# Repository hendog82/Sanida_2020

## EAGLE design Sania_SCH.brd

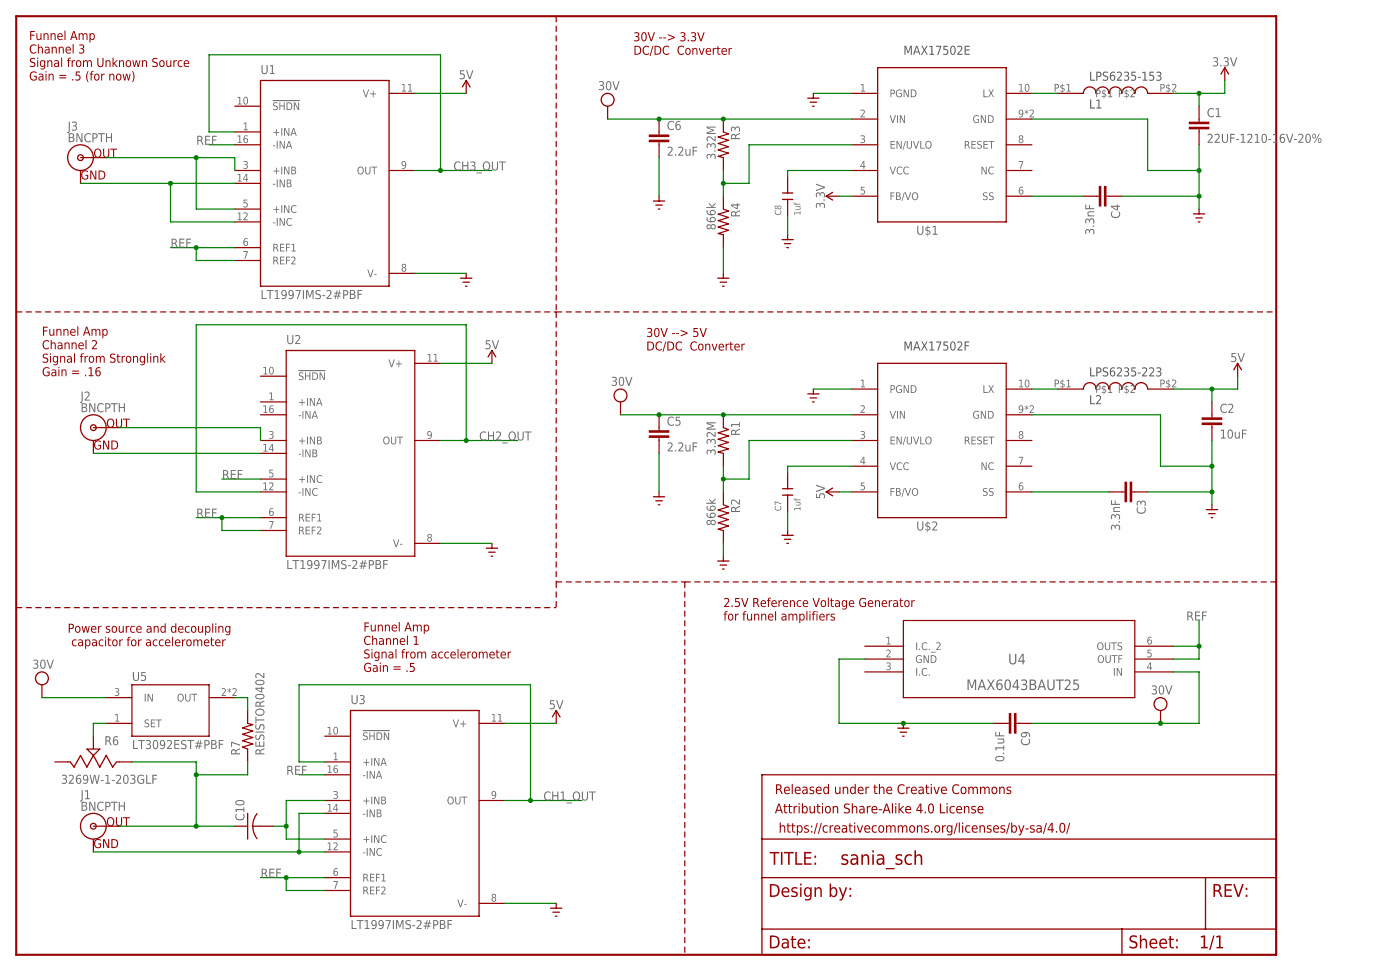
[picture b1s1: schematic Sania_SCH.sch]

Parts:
C1: 22UF-1210-16V-20%; 1210
C2: 10uF; 1210
C3, C4: 3.3nF; 0603
C5, C6: 2.2uF; 1206
C7, C8: 1uf; C0805
C9: 0.1uF; 0603
C10: C-USC0603; C0603
FRAME1: FRAME-LETTER; CREATIVE_COMMONS
J1, J2, J3: BNCPTH; BNC
L1: LPS6235-153; LPS6235
L2: LPS6235-223; LPS6235
R1, R3: 3.32M; R0805
R2, R4: 866k; R0805
R6: 3269W-1-203GLF
R7: RESISTOR0402; 0402-RES
U1, U2, U3: LT1997IMS-2#PBF; SOP50P490X110-12N
U4: MAX6043BAUT25; 21-0058I
U5: LT3092EST#PBF; IC_LT3092EST#PBF
U$1: MAX17502E; SON50P200X300X80-11T90X200N
U$2: MAX17502F; SON50P200X300X80-11T90X200N

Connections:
3.3V: C1.1, L1.P$2, U$1.5 (FB/VO)
5V: C2.1, L2.P$2, U1.11 (V+), U2.11 (V+), U3.11 (V+), U$2.5 (FB/VO)
CH1_OUT: U3.1 (+INA), U3.9 (OUT)
CH2_OUT: U2.9 (OUT), U2.12 (-INC)
CH3_OUT: U1.1 (+INA), U1.9 (OUT)
GND: C1.2, C2.2, C3.1, C4.1, C5.2, C6.2, C7.1, C8.1, C9.2, R2.2, R4.2, U1.8 (V-), U2.8 (V-), U3.8 (V-), U4.2 (GND), U$1.1 (PGND), U$1.9 (GND), U$1.11 (GND), U$2.1 (PGND), U$2.9 (GND), U$2.11 (GND)
unnamed: L1.P$1, U$1.10 (LX)
unnamed: L2.P$1, U$2.10 (LX)
unnamed: C8.2, U$1.4 (VCC)
unnamed: R3.2, R4.1, U$1.3 (EN/UVLO)
unnamed: C4.2, U$1.6 (SS)
unnamed: C3.2, U$2.6 (SS)
unnamed: C7.2, U$2.4 (VCC)
unnamed: R1.2, R2.1, U$2.3 (EN/UVLO)
unnamed: J3.S (OUT), U1.3 (+INB), U1.5 (+INC)
unnamed: J3.GND, U1.12 (-INC), U1.14 (-INB)
unnamed: J2.S (OUT), U2.3 (+INB)
unnamed: J2.GND, U2.14 (-INB)
unnamed: C10.2, U3.3 (+INB), U3.5 (+INC)
unnamed: J1.GND, U3.12 (-INC), U3.14 (-INB)
unnamed: R7.2, U5.2 (OUT), U5.4 (OUT)
unnamed: R6.2, U5.1 (SET)
unnamed: C10.1, J1.S (OUT), R6.3, R7.1
REF: U1.6 (REF1), U1.7 (REF2), U1.16 (-INA), U2.5 (+INC), U2.6 (REF1), U2.7 (REF2), U3.6 (REF1), U3.7 (REF2), U3.16 (-INA), U4.5 (OUTF), U4.6 (OUTS)
VCC: C5.1, C6.1, C9.1, R1.1, R3.1, U4.4 (IN), U5.3 (IN), U$1.2 (VIN), U$2.2 (VIN)

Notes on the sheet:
2.5V Reference Voltage Generator for funnel amplifiers
30V --> 3.3V DC/DC Converter
30V --> 5V DC/DC Converter
Funnel Amp Channel 1 Signal from accelerometer Gain = .5
Funnel Amp Channel 2 Signal from Stronglink Gain = .16
Funnel Amp Channel 3 Signal from Unknown Source Gain = .5 (for now)
Power source and decoupling capacitor for accelerometer

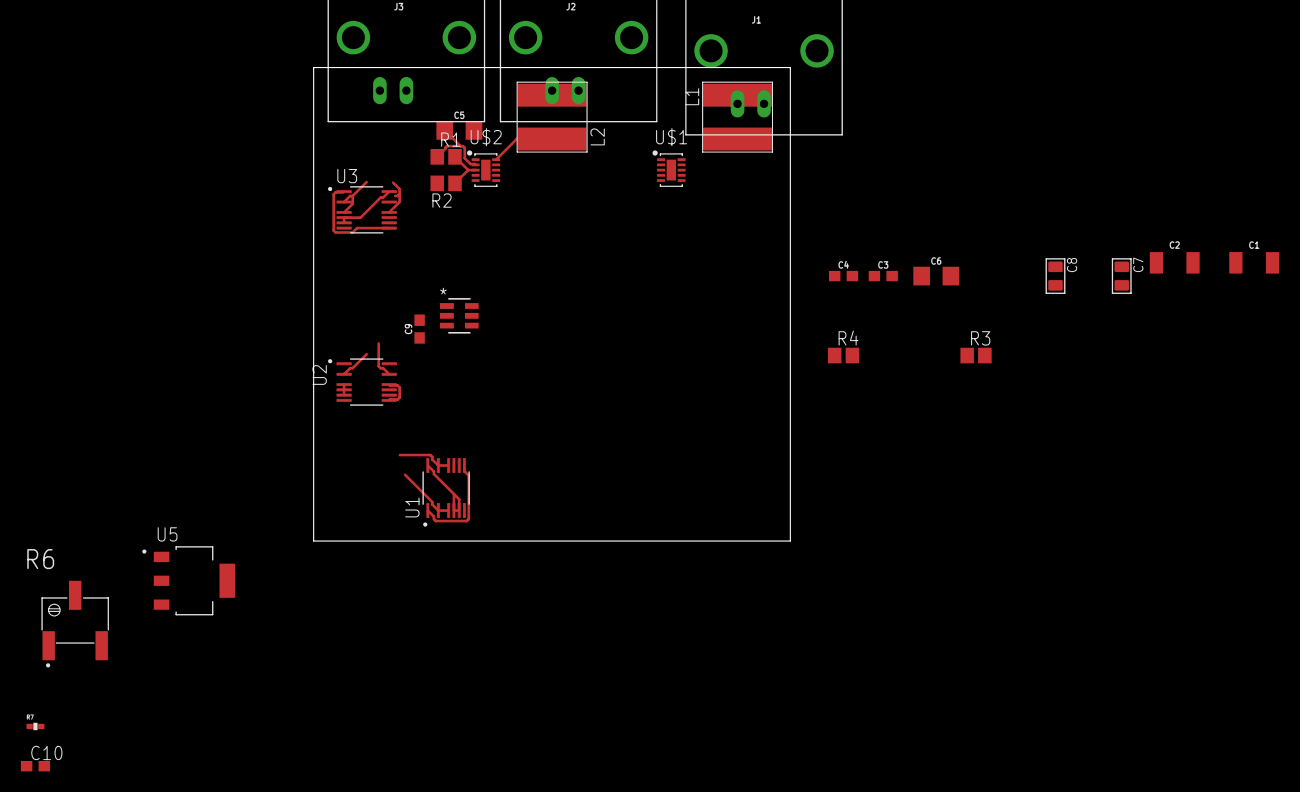
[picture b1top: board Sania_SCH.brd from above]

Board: 2 copper layers, 45.7 x 45.4 mm, 29 parts (0 on the bottom side), 25 nets.

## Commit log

2020-01-21 deleted save states

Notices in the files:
parts and their libraries:
SparkFun-Capacitors: Licensing: Creative Commons ShareAlike 4.0 International - https://creativecommons.org/licenses/by-sa/4.0
SparkFun-Aesthetics: Released under the Creative Commons Attribution Share-Alike 4.0 License
SparkFun-Aesthetics: https://creativecommons.org/licenses/by-sa/4.0
